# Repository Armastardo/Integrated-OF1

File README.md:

# Integrated-OF1
RaspberryPi Pico-powered board compatible with Rev 1 Heavy and Rev 1/2 Light cases (to be sold in waves on the Frame1.gg website).

Design files are available in this repository. Production files for JLCPCB in the releases page. Tested working and fitting previously mentioned Frame 1 cases.

## Table of contents
* [Features](#features)
* [Usage](#usage)
* [Acknowledgements](#acknowledgements)

## Features
- USB-C to GCC and USB-C to N64 cable compatible with integrated port.
- Uses [HayBox](https://github.com/JonnyHaystack/HayBox) and [Pico Rectangle](https://github.com/JulienBernard3383279/pico-rectangle) default pinout.

## Usage
1. Order via JLCPCB using the production files in the releases page.
2. Connect them to the PC and the first time it'll show up as a mass storage device.
3. Drop your prefered firmware in uf2 format and once it disconnects it should be good to go.
	- If you connect while pressing the BOOT button (or shorting the pads in the back), it'll show again as a mass storage device so you can update the firmware or replace it.
	- You can also press START on connect if using HayBox or CRIGHT if using pico-rectangle.

## Acknowledgements:
- Greg Turbo: For creating the Frame1 and the Open Frame 1.
- Crane's Lab discord server: For the community that inspired me to create things like this.

### Made using the Open Rectangle Template
OpenRectangleTemplate project - https://github.com/Armastardo/OpenRectangleTemplate

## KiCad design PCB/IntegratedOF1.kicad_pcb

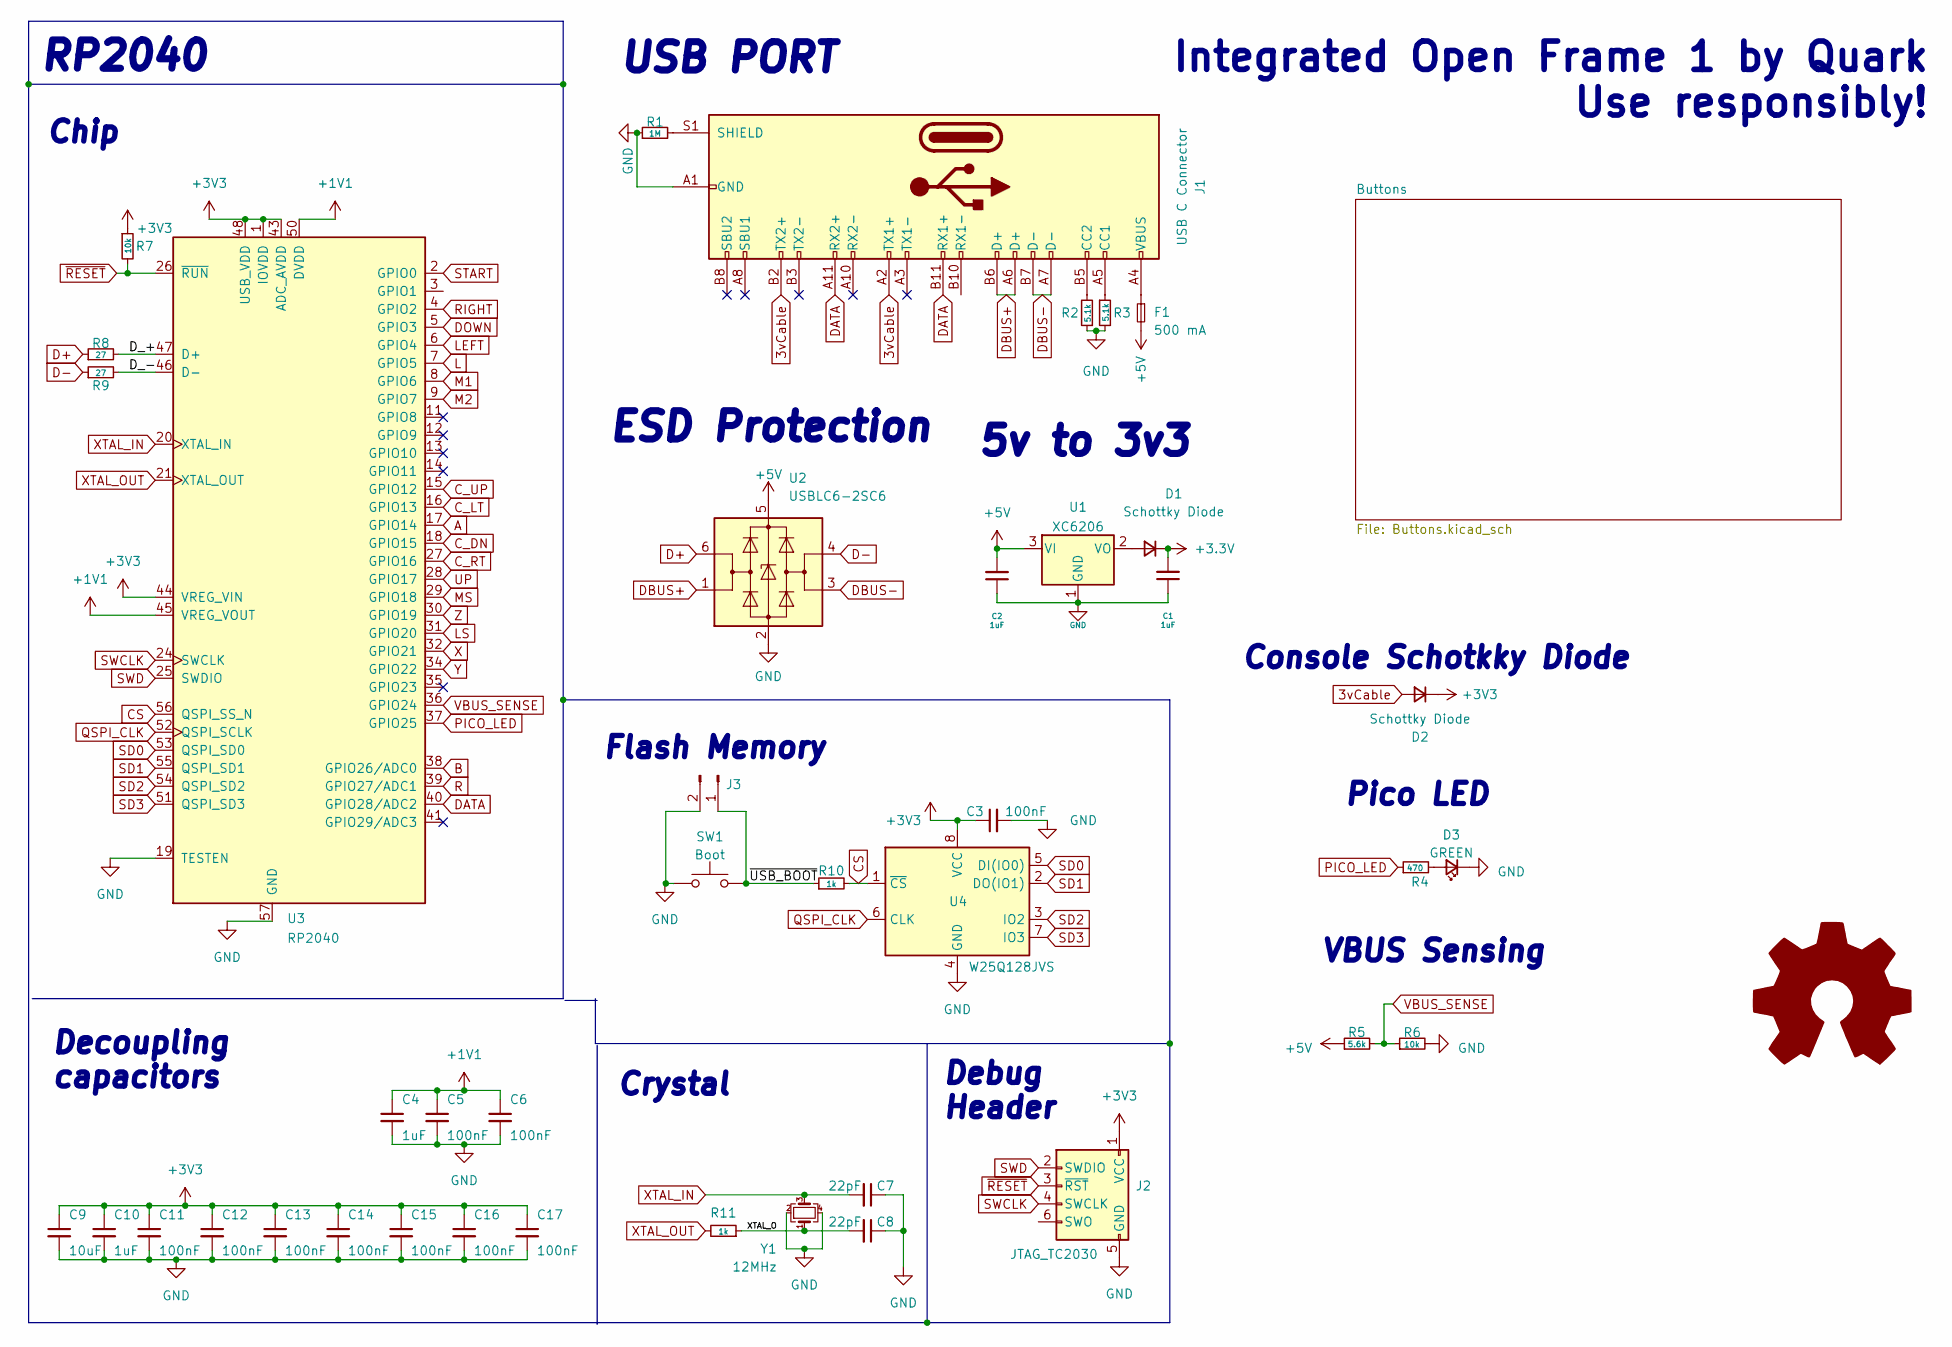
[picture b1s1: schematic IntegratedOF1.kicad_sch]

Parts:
C1, C2, C4, C10: 1uF; C_0402_1005Metric; LCSC C52923
C3, C5, C6, C11, C12, C13, C14, C15, C16, C17: 100nF; C_0402_1005Metric; LCSC C1525
C7, C8: 22pF; C_0402_1005Metric; LCSC C1555
C9: 10uF; C_0402_1005Metric; LCSC C15525
D1, D2: Schottky Diode; D_SOD-123; LCSC C8598
D3: GREEN; LED_0805_2012Metric; LCSC C2297
F1: 500 mA; Fuse_1206_3216Metric; LCSC C2836286
J1: USB C Connector; TYPE-C_24P_QCHT; LCSC C456013
J2: JTAG_TC2030; CON_TC2030_outlined
J3: Conn_01x02_Pin; PinHeader_1x02_P2.54mm_Vertical
R1: 1M; R_0603_1608Metric; LCSC C22935
R2, R3: 5.1k; R_0402_1005Metric; LCSC C25905
R4: 470; R_0402_1005Metric; LCSC C25117
R5: 5.6k; R_0603_1608Metric; LCSC C23189
R6: 10k; R_0603_1608Metric; LCSC C25804
R7: 10k; R_0402_1005Metric; LCSC C25744
R8, R9: 27; R_0603_1608Metric; LCSC C25190
R10, R11: 1k; R_0402_1005Metric; LCSC C11702
SW1: Boot; SW_SPST_SKQG_WithStem; LCSC C318884
SYM1: Logo_Open_Hardware_Large; OSHW-Logo_28.5x30mm_SilkScreen
U1: XC6206; SOT-23; LCSC C5446
U2: USBLC6-2SC6; SOT-23-6; LCSC C2827654
U3: RP2040; RP2040-QFN-56; LCSC C2040
U4: W25Q128JVS; SOIC-8_5.23x5.23mm_P1.27mm; LCSC C97521
Y1: 12MHz; Crystal_SMD_3225-4Pin_3.2x2.5mm; LCSC C9002

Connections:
3vCable: D2.2 (A), J1.A2 (TX1+), J1.B2 (TX2+)
+1V1: C4.1, C5.1, C6.1, U3.23 (DVDD), U3.45 (VREG_VOUT), U3.50 (DVDD)
+5V: C2.2, F1.2, R5.1, U1.3 (VI), U2.5 (VBUS)
/D_+: R8.2, U3.47 (D+)
/D_-: R9.2, U3.46 (D-)
/XTAL_O: C8.2, R11.1, Y1.1
/~USB_BOOT: J3.1, R10.1, SW1.2
A: U3.17 (GPIO14); also elsewhere on the board
B: U3.38 (GPIO26/ADC0); also elsewhere on the board
CS: R10.2, U3.56 (QSPI_SS_N), U4.1 (~CS)
C_DN: U3.18 (GPIO15); also elsewhere on the board
C_LT: U3.16 (GPIO13); also elsewhere on the board
C_RT: U3.27 (GPIO16); also elsewhere on the board
C_UP: U3.15 (GPIO12); also elsewhere on the board
D+: R8.1, U2.6 (I/O1)
D-: R9.1, U2.4 (I/O2)
DATA: J1.A11 (RX2+), J1.B11 (RX1+), U3.40 (GPIO28/ADC2)
DBUS+: J1.A6 (D+), J1.B6 (D+), U2.1 (I/O1)
DBUS-: J1.A7 (D-), J1.B7 (D-), U2.3 (I/O2)
DOWN: U3.5 (GPIO3); also elsewhere on the board
GND: C1.1, C2.1, C3.2, C4.2, C5.2, C6.2, C7.1, C8.1, C9.2, C10.2, C11.2, C12.2, C13.2, C14.2, C15.2, C16.2, C17.2, D3.1 (K), J1.A1 (GND), J1.A12 (GND), J1.B1 (GND), J1.B12 (GND), J2.5 (GND), J3.2, R1.1, R2.1, R3.2, R6.2, SW1.1, U1.1 (GND), U2.2 (GND), U3.19 (TESTEN), U3.57 (GND), U4.4 (GND), Y1.2, Y1.4; also elsewhere on the board
L: U3.7 (GPIO5); also elsewhere on the board
LEFT: U3.6 (GPIO4); also elsewhere on the board
LS: U3.31 (GPIO20); also elsewhere on the board
M1: U3.8 (GPIO6); also elsewhere on the board
M2: U3.9 (GPIO7); also elsewhere on the board
MS: U3.29 (GPIO18); also elsewhere on the board
unnamed: D1.2 (A), U1.2 (VO)
unnamed: D3.2 (A), R4.2
unnamed: F1.1, J1.A4 (VBUS), J1.A9 (VBUS), J1.B4 (VBUS), J1.B9 (VBUS)
unnamed: J1.A5 (CC1), R3.1
unnamed: J1.B5 (CC2), R2.2
unnamed: J1.S1 (SHIELD), R1.2
PICO_LED: R4.1, U3.37 (GPIO25)
QSPI_CLK: U3.52 (QSPI_SCLK), U4.6 (CLK)
R: U3.39 (GPIO27/ADC1); also elsewhere on the board
RIGHT: U3.4 (GPIO2); also elsewhere on the board
SD0: U3.53 (QSPI_SD0), U4.5 (DI(IO0))
SD1: U3.55 (QSPI_SD1), U4.2 (DO(IO1))
SD2: U3.54 (QSPI_SD2), U4.3 (IO2)
SD3: U3.51 (QSPI_SD3), U4.7 (IO3)
START: U3.2 (GPIO0); also elsewhere on the board
SWCLK: J2.4 (SWCLK), U3.24 (SWCLK)
SWD: J2.2 (SWDIO), U3.25 (SWDIO)
UP: U3.28 (GPIO17); also elsewhere on the board
VBUS_SENSE: R5.2, R6.1, U3.36 (GPIO24)
X: U3.32 (GPIO21); also elsewhere on the board
XTAL_IN: C7.2, U3.20 (XTAL_IN), Y1.3
XTAL_OUT: R11.2, U3.21 (XTAL_OUT)
Y: U3.34 (GPIO22); also elsewhere on the board
Z: U3.30 (GPIO19); also elsewhere on the board
~RESET: J2.3 (~RST), R7.2, U3.26 (~RUN)

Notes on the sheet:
Integrated Open Frame 1 by Quark Use responsibly!
5v to 3v3
ESD Protection
RP2040
Console Schotkky Diode
USB PORT
Flash Memory
Debug Header
Pico LED
VBUS Sensing
Chip
Decoupling capacitors
Crystal

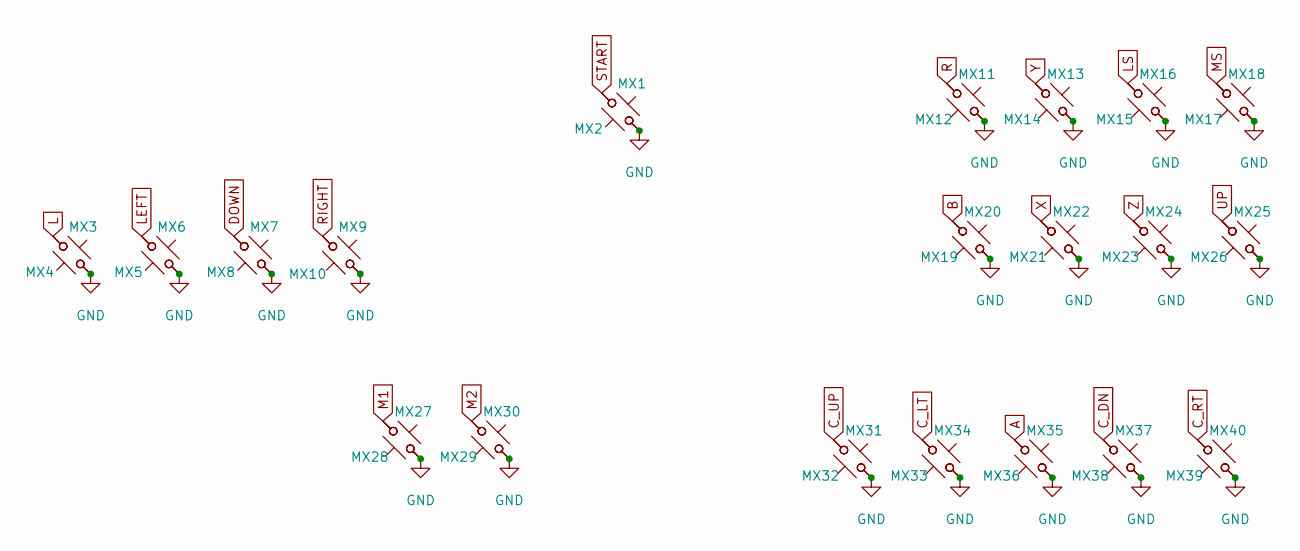
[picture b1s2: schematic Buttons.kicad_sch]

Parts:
MX1, MX3, MX6, MX7, MX9, MX11, MX13, MX16, MX18, MX20, MX22, MX24, MX25, MX27, MX30, MX31, MX34, MX35, MX37, MX40: MX_SW_HS; SW_MX_HS_1u
MX2, MX4, MX5, MX8, MX10, MX12, MX14, MX15, MX17, MX19, MX21, MX23, MX26, MX28, MX29, MX32, MX33, MX36, MX38, MX39: MX_SW_solder; SW_MX_1u

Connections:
A: MX35.1, MX36.2; also elsewhere on the board
B: MX19.2, MX20.1; also elsewhere on the board
C_DN: MX37.1, MX38.2; also elsewhere on the board
C_LT: MX33.2, MX34.1; also elsewhere on the board
C_RT: MX39.2, MX40.1; also elsewhere on the board
C_UP: MX31.1, MX32.2; also elsewhere on the board
DOWN: MX7.1, MX8.2; also elsewhere on the board
GND: MX1.2, MX2.1, MX3.2, MX4.1, MX5.1, MX6.2, MX7.2, MX8.1, MX9.2, MX10.1, MX11.2, MX12.1, MX13.2, MX14.1, MX15.1, MX16.2, MX17.1, MX18.2, MX19.1, MX20.2, MX21.1, MX22.2, MX23.1, MX24.2, MX25.2, MX26.1, MX27.2, MX28.1, MX29.1, MX30.2, MX31.2, MX32.1, MX33.1, MX34.2, MX35.2, MX36.1, MX37.2, MX38.1, MX39.1, MX40.2; also elsewhere on the board
L: MX3.1, MX4.2; also elsewhere on the board
LEFT: MX5.2, MX6.1; also elsewhere on the board
LS: MX15.2, MX16.1; also elsewhere on the board
M1: MX27.1, MX28.2; also elsewhere on the board
M2: MX29.2, MX30.1; also elsewhere on the board
MS: MX17.2, MX18.1; also elsewhere on the board
R: MX11.1, MX12.2; also elsewhere on the board
RIGHT: MX9.1, MX10.2; also elsewhere on the board
START: MX1.1, MX2.2; also elsewhere on the board
UP: MX25.1, MX26.2; also elsewhere on the board
X: MX21.2, MX22.1; also elsewhere on the board
Y: MX13.1, MX14.2; also elsewhere on the board
Z: MX23.2, MX24.1; also elsewhere on the board

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
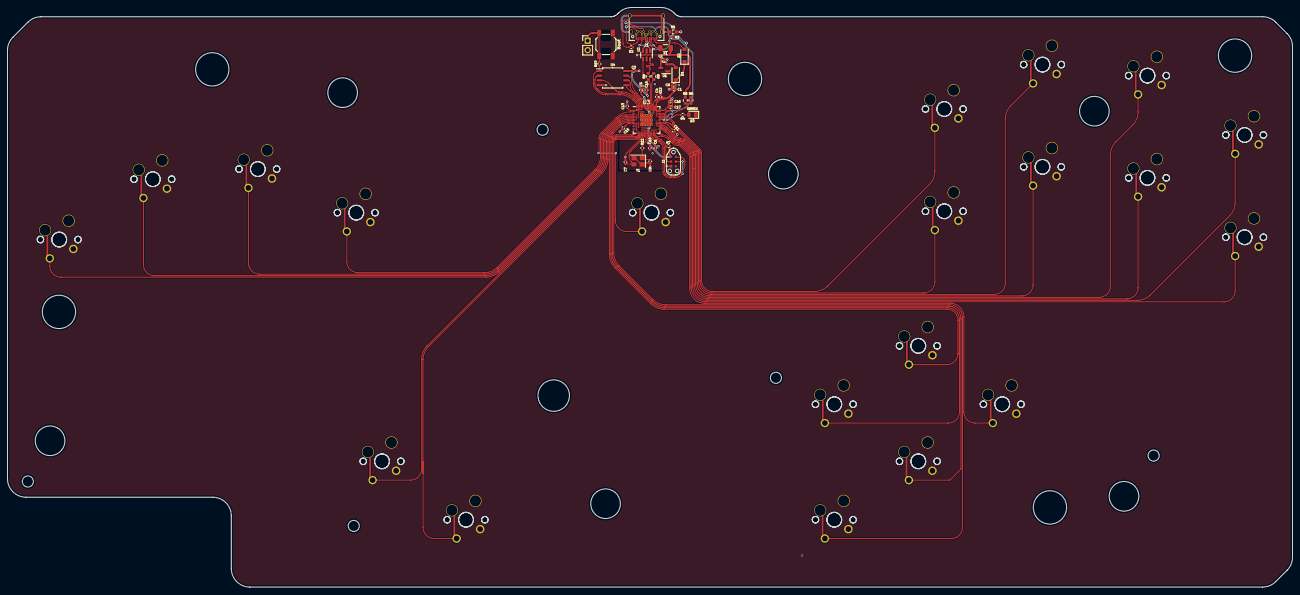
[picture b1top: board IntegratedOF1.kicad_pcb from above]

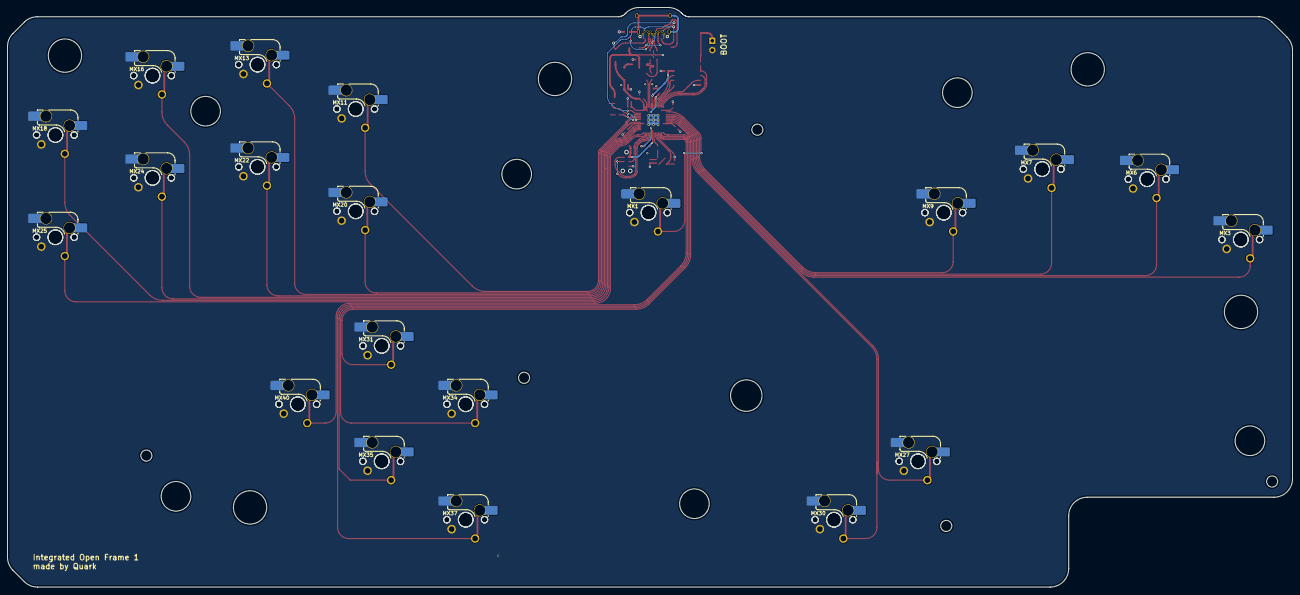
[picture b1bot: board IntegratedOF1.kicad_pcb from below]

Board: 2 copper layers, 347.0 x 156.5 mm, 81 parts (20 on the bottom side), 53 nets.

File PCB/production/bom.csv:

Designator,Footprint,Quantity,Value,LCSC Part #
"C1, C10, C2, C4",0402,4,1uF,C52923
"C11, C12, C13, C14, C15, C16, C17, C3, C5, C6",0402,10,100nF,C1525
"C7, C8",0402,2,22pF,C1555
C9,0402,1,10uF,C15525
"D1, D2",D_SOD-123,2,Schottky Diode,C8598
D3,0805,1,GREEN,C2297
F1,1206,1,500 mA,C2836286
J1,TYPE-C_24P_QCHT,1,USB C Connector,C456013
"MX1, MX11, MX13, MX16, MX18, MX20, MX22, MX24, MX25, MX27, MX3, MX30, MX31, MX34, MX35, MX37, MX40, MX6, MX7, MX9",SW_MX_HS_1u,20,MX_SW_HS,
R1,0603,1,1M,C22935
"R10, R11",0402,2,1k,C11702
"R2, R3",0402,2,5.1k,C25905
R4,0402,1,470,C25117
R5,0603,1,5.6k,C23189
R6,0603,1,10k,C25804
R7,0402,1,10k,C25744
"R8, R9",0603,2,27,C25190
SW1,SW_SPST_SKQG_WithStem,1,Boot,C5156480
U1,SOT-23,1,XC6206,C5446
U2,SOT-23-6,1,USBLC6-2SC6,C2827654
U3,RP2040-QFN-56,1,RP2040,C2040
U4,SOIC-8_5.23x5.23mm_P1.27mm,1,W25Q128JVS,C97521
Y1,Crystal_SMD_3225-4Pin_3.2x2.5mm,1,12MHz,C9002

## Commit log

2023-05-22 Initial commit, done.
2023-05-22 Adjusted BOM and Readme.md
    Added a part number for the BOOT button, added Acknowledgements section. Fixed a typo
2023-05-22 Adjusted PCB and BOM
    - Adjusted PCB to add missing screw hole and repositioned one more according to the plate file.
    - Move the shield resistor to a new position where it shouldn't interfere with some cases.
    - Added a new cutout in the PCB so it's easier to extract from a F1 case.
    - Changed Schottky diode and boot button part # so they use a basic part instead of an extended one.
2024-02-28 v1.0
2024-03-11 Adjusted push button to the correct part number
